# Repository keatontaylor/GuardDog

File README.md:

Guard Dog README
================

After many weeks of not updating this blog I've finally managed to get around to completing the majority of the hardware requirements for the open source security system I've been developing. I've migrated from using an Arduino for detecting events to using a beagle-bone so that I could centralize processing of all the events and provide a single platform that could be used for installation.

The entire project is still a large work in progress but with the bulk of the hardware implementation complete my focus now shifts towards the software aspects of the device. A great deal of though has gone into the exact design of the software and how it will function in an intelligent way.

Using the GPIO pins on the beagle-bone entry and exit events are detected and logged. Using these events an algorithm is being developed to analyze the data. Clustering and the development of a neural net will be used to determine the likelihood of an event trigger for a specific timezone. Overtime the system will learn your habits and patterns will emerge. Using these patterns and the structure provided in the neural net notifications will be sent to assigned users depending on the likelihood of a false entry.

Using this method it is theorized that in a little as a month the system should be able to interpret when it is likely for someone to be home and when it is likely some isn't. Although this system in theory provides an extremely accurate way of detecting events that don't fall within the typical norm, it does present issues that will need to be addressed in future versions of the software.

The largest of the concerns is that data analysis does not inherently have a way of detecting of someone is already home or has been home. This presents itself as an issue when the occupant walks into a zone or triggers an event the system was not able to anticipate, ultimately triggering a notification when in reality no notification needed to be sent out. To resolve this issue the system has to be able to detect occupancy, and to do so a method of detecting the rough number of people in the home needs to be developed.

To accomplish this theory was devised that would allow the system to detect the direction of motion by calculating events triggered down to the nearest 10 milliseconds. This works by detecting a motion event before a door event or vice versa giving the system a reasonable assessment of whether someone entered or left the premisses. To counteract the systems inability to detect the number of occupants that entered the system will calculate the total number of motion detection events within one hour of the entry or exit to determine the approximate occupancy.

During my research this method of determining occupancy  was able to predict with around 80% accuracy the number of occupants in the home with as little as two motion detection sensors strategically place around active areas of the home.

Much work needs to be done and theory needs to be proven in real world testing but all-in-all the development of the system is progressing. Hopefully a large chunk of the system will be completed within the coming months.

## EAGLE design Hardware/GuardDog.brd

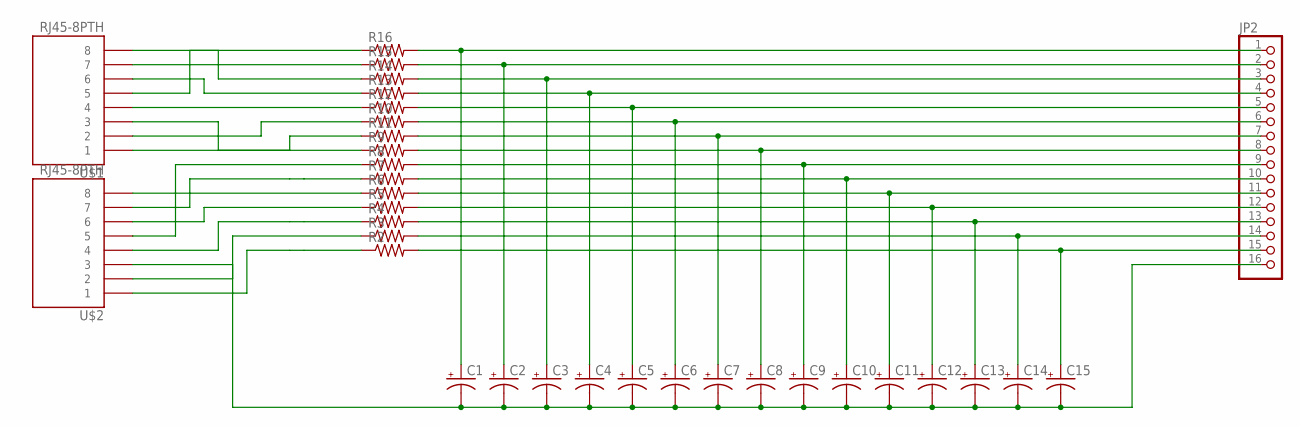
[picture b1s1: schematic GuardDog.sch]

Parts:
C1, C2, C3, C4, C5, C6, C7, C8, C9, C10, C11, C12, C13, C14, C15: CAP_POLPTH2; CPOL-RADIAL-10UF-25V
JP2: PINHD-1X16; 1X16
R2, R3, R4, R5, R6, R7, R8, R9, R10, R11, R12, R13, R14, R15, R16: R-US_0204/5; 0204/5
U$1, U$2: RJ45-8PTH; RJ45-8

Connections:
unnamed: R15.1, U$1.7
unnamed: C2.1 (+), JP2.2, R15.2
unnamed: R16.1, U$1.5
unnamed: C1.1 (+), JP2.1, R16.2
unnamed: R14.1, U$1.8
unnamed: C3.1 (+), JP2.3, R14.2
unnamed: R13.1, U$1.6
unnamed: C4.1 (+), JP2.4, R13.2
unnamed: R12.1, U$1.4
unnamed: C5.1 (+), JP2.5, R12.2
unnamed: C6.1 (+), JP2.6, R10.2
unnamed: R10.1, U$1.2
unnamed: C7.1 (+), JP2.7, R11.2
unnamed: C8.1 (+), JP2.8, R9.2
unnamed: R9.1, U$1.3
unnamed: R8.1, U$2.5
unnamed: R7.1, U$2.7
unnamed: R6.1, U$2.8
unnamed: R4.1, U$2.4
unnamed: R5.1, U$2.6
unnamed: R3.1, U$2.2
unnamed: R2.1, U$2.1
unnamed: C9.1 (+), JP2.9, R8.2
unnamed: C10.1 (+), JP2.10, R7.2
unnamed: C11.1 (+), JP2.11, R6.2
unnamed: C12.1 (+), JP2.12, R5.2
unnamed: C13.1 (+), JP2.13, R4.2
unnamed: C14.1 (+), JP2.14, R3.2
unnamed: C15.1 (+), JP2.15, R2.2
unnamed: R11.1, U$1.1
unnamed: C1.2 (-), C2.2 (-), C3.2 (-), C4.2 (-), C5.2 (-), C6.2 (-), C7.2 (-), C8.2 (-), C9.2 (-), C10.2 (-), C11.2 (-), C12.2 (-), C13.2 (-), C14.2 (-), C15.2 (-), JP2.16, U$2.3

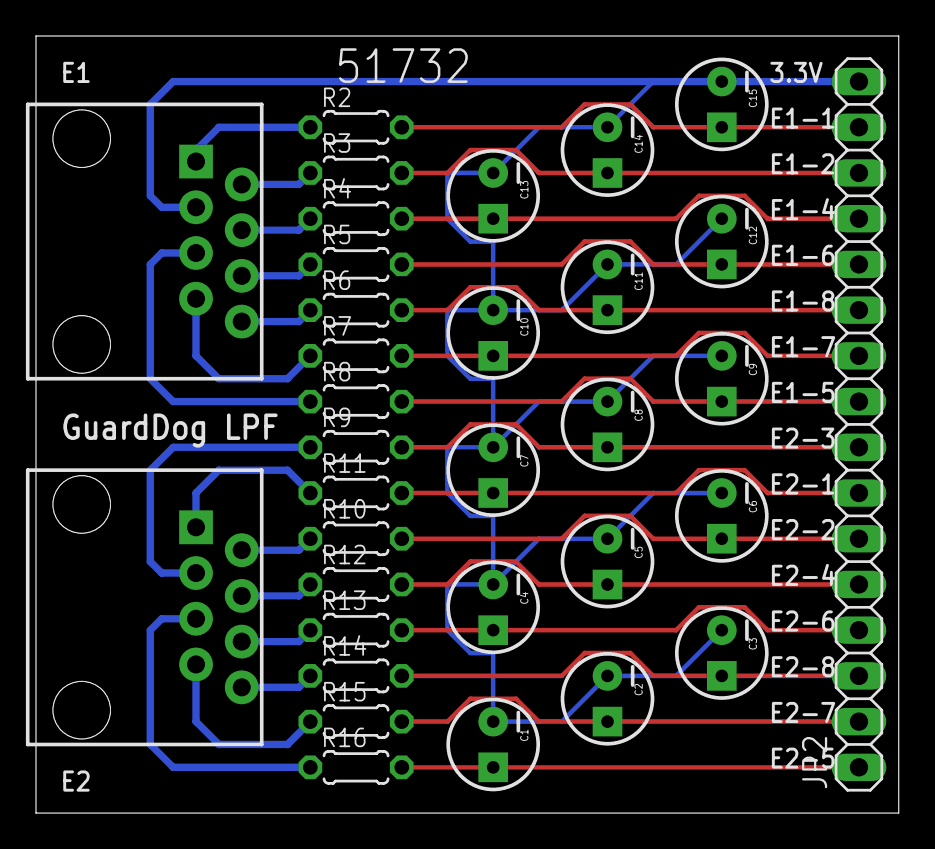
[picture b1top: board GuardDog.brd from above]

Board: 2 copper layers, 47.9 x 43.2 mm, 33 parts (0 on the bottom side), 31 nets.

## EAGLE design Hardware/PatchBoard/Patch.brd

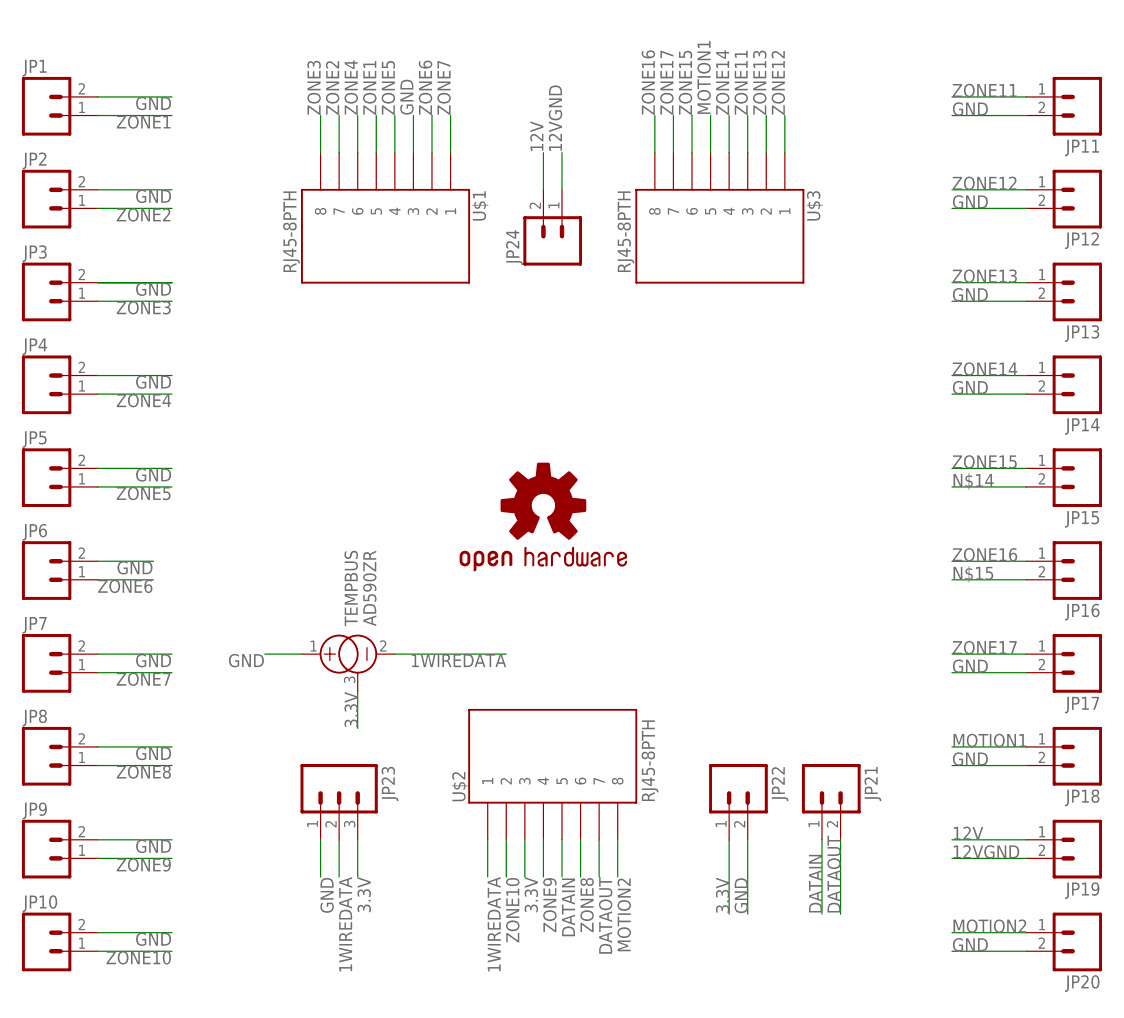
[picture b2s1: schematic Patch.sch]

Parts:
JP1, JP2, JP3, JP4, JP5, JP6, JP7, JP8, JP9, JP10, JP11, JP12, JP13, JP14, JP15, JP16, JP17, JP18, JP19, JP20, JP21, JP22: M023.5MM; SCREWTERMINAL-3.5MM-2
JP23: M03SCREW; SCREWTERMINAL-3.5MM-3
JP24: M025MM; SCREWTERMINAL-5MM-2
TEMPBUS: AD590ZR; TO92
U$1, U$2, U$3: RJ45-8PTH; RJ45-8
U$4: OSHW-LOGOL; OSHW-LOGO-L

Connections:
1WIREDATA: JP23.2, TEMPBUS.2 (-), U$2.1
3.3V: JP22.1, JP23.3, TEMPBUS.3 (CAN), U$2.3
12V: JP19.1, JP24.2
12VGND: JP19.2, JP24.1
DATAIN: JP21.1, U$2.5
DATAOUT: JP21.2, U$2.7
GND: JP1.2, JP2.2, JP3.2, JP4.2, JP5.2, JP6.2, JP7.2, JP8.2, JP9.2, JP10.2, JP11.2, JP12.2, JP13.2, JP14.2, JP17.2, JP18.2, JP20.2, JP22.2, JP23.1, TEMPBUS.1 (+), U$1.3
MOTION1: JP18.1, U$3.5
MOTION2: JP20.1, U$2.8
ZONE1: JP1.1, U$1.5
ZONE2: JP2.1, U$1.7
ZONE3: JP3.1, U$1.8
ZONE4: JP4.1, U$1.6
ZONE5: JP5.1, U$1.4
ZONE6: JP6.1, U$1.2
ZONE7: JP7.1, U$1.1
ZONE8: JP8.1, U$2.6
ZONE9: JP9.1, U$2.4
ZONE10: JP10.1, U$2.2
ZONE11: JP11.1, U$3.3
ZONE12: JP12.1, U$3.1
ZONE13: JP13.1, U$3.2
ZONE14: JP14.1, U$3.4
ZONE15: JP15.1, U$3.6
ZONE16: JP16.1, U$3.8
ZONE17: JP17.1, U$3.7

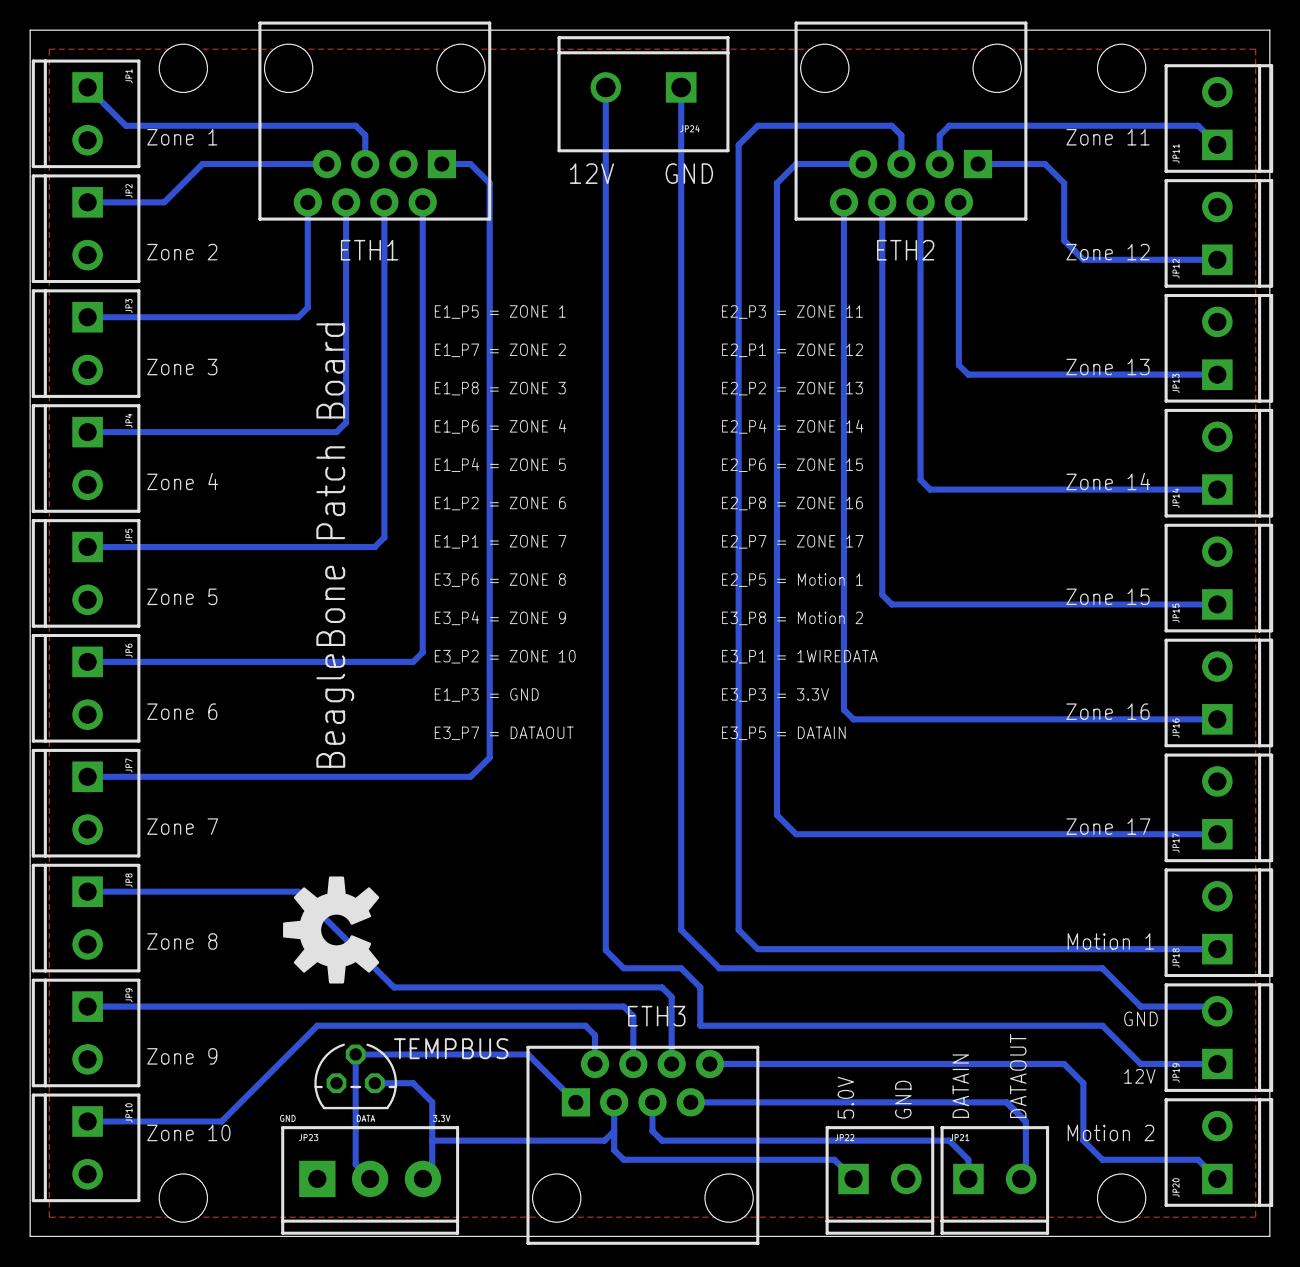
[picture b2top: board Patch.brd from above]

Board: 2 copper layers, 82.2 x 80.0 mm, 29 parts (0 on the bottom side), 26 nets.

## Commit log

2012-08-12 inital commit
2012-08-12 Added basic structure of the algorythim.
2012-08-13 Added PCB designs.
2012-08-13 Removing PCB junk
2012-08-14 Added API code.
2012-08-16 Added HMAC authentication for API.
2012-08-16 Added timestamp verification. (Replay protection)
2012-08-16 Added README file for API and fixed the hash comparision.
2012-08-16 Made the api folder lower cased for consistancy.
2012-08-21 Removed some files
2012-08-21 Cleaned things up a bit.
2012-08-21 Added .DS_Store
2012-08-23 Removed redudant pins.py file as the data is now pulled from a database in the main.py file.
2012-08-23 Cleaned up.
2012-08-23 Added folder.
2012-08-23 Added zones method to api.
2012-08-24 Spring cleaning.
2012-08-24 Cleaning up code.
2012-08-24 Cleaning code.
2012-08-24 Cleaing code.
2012-08-28 More skeleton, some prototyping
    Added some additional skeleton and began a prototype of
    developClusters()
2012-08-29 Added TODO
2012-08-29 Added more TODO
2012-08-29 Added class for zones to remove the use of a global method.
2012-08-29 Removed un-needed code like the database queue that checks if the database if avalible. This code was no longer needed after the conversion to sqlite. Also removed all globals and replaced them with 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
2012-08-29 Cleaned up the pinStructure init.
2012-08-29 Changed the database location in api/index.php and cleaned up some code in main.py
2012-08-29 Cleaned up line spacing
2012-08-29 Changed line spacing to 4. Added framework for reusable classes and methods.
2012-08-29 Fixed line spacing to follow standard of "4" spaces.
2012-08-29 Fixed an issue with the return statement in the getZones() method.
2012-08-29 Added close statement for database in getZones()
2012-08-30 Added inc folder for includes and moved reusable code into the framwork file. Modified main to work with the framework file.
2012-08-30 Deleted framework from root dir.
2012-08-30 Added ,gitignore to git.
2012-08-30 Added gitignore
2012-08-30 Fixed line spacing.
2012-08-30 Removed duplicate files
2012-08-30 Removed except statements, need to add error catching later.
2012-08-30 Changed commenting to docstrings and cleaned up code.
2012-08-30 Added license and fixed doctoring issues.
2012-08-30 Fixed if else statement
2012-09-01 Added stDev code
    Added some code to calculate the mean and standard deviation.
2012-09-16 Did some thinking/prototyping
    Did some thinking/prototyping on how to build the clusters, how to
    find the nearest point in each cluster in a minimal-work way
2017-02-17 Added Untitled Diagram.xml
2017-02-17 UML Monopoly
2017-02-17 Added Flow.xml

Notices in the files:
parts and their libraries:
SparkFun: Licensing: CC v3.0 Share-Alike You are welcome to use this library for commercial purposes.
